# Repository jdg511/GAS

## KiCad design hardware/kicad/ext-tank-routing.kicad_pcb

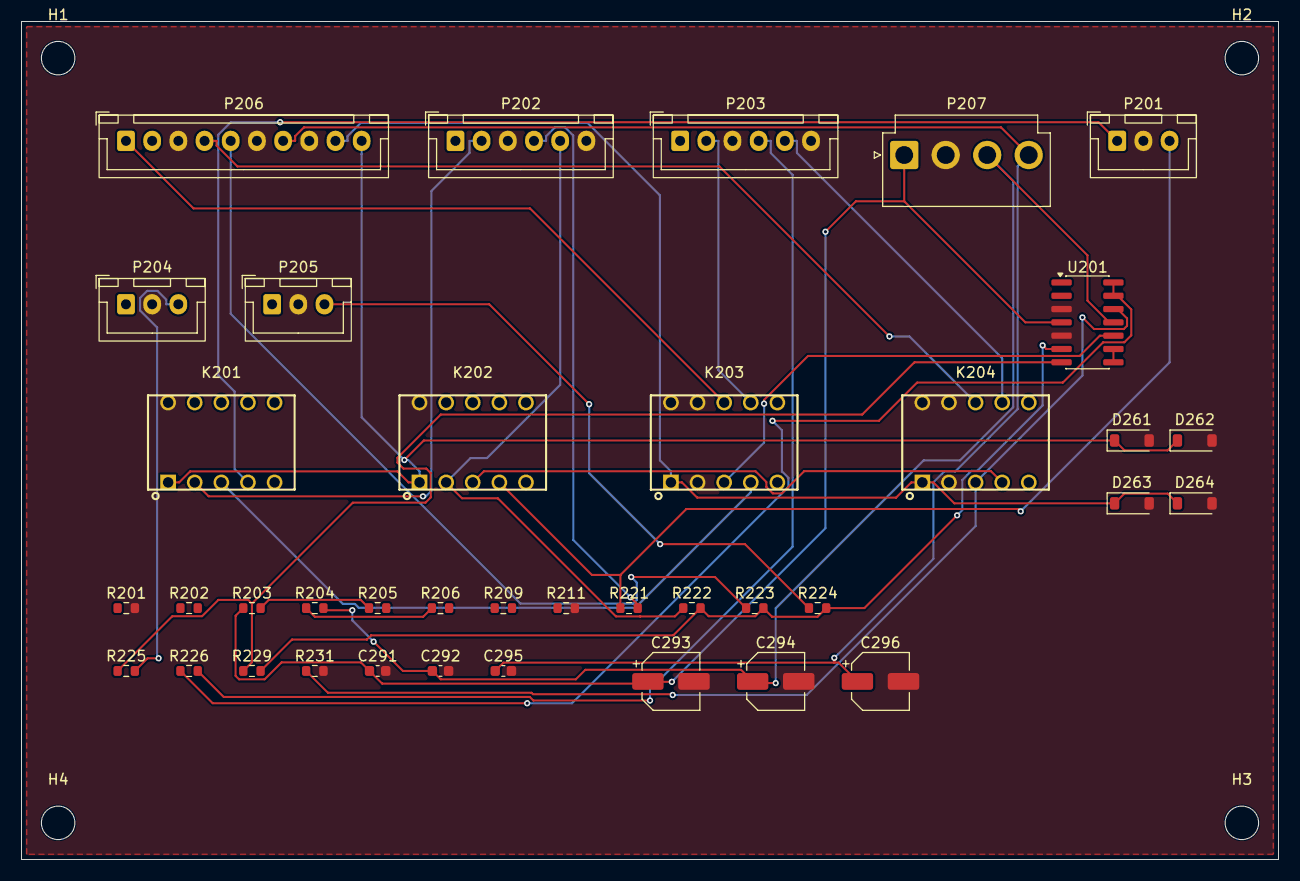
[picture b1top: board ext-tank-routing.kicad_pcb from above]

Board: 2 copper layers, 120.0 x 80.0 mm, 42 parts (0 on the bottom side), 29 nets.

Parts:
C291, C292, C295: 100nF; C_0603_1608Metric
C293, C294, C296: 10uF; CP_Elec_5x5.8
D261, D262, D263, D264: 1N4148W; D_SOD-123
H1, H2, H3, H4: M3 NPTH; MountingHole_3.2mm_M3
K201, K202, K203, K204: TQ2-5V; Relay_DPDT_Panasonic_TQ2
P201: JIO-WETSEND; JST_XH_B3B-XH-A_1x03_P2.50mm_Vertical
P202: JTR-PRI; JST_XH_B6B-XH-A_1x06_P2.50mm_Vertical
P203: JTR-SEC; JST_XH_B6B-XH-A_1x06_P2.50mm_Vertical
P204: JTR-XFADE; JST_XH_B3B-XH-A_1x03_P2.50mm_Vertical
P205: JFB-INJ; JST_XH_B3B-XH-A_1x03_P2.50mm_Vertical
P206: JER-CTRL; JST_XH_B10B-XH-A_1x10_P2.50mm_Vertical
P207: JER-PWR; JST_VH_B4P-VH_1x04_P3.96mm_Vertical
R201, R205, R206, R221, R225, R226: 100R; R_0603_1608Metric
R202, R203, R204, R209, R222, R223, R224, R229: 20k; R_0603_1608Metric
R211, R231: 100k; R_0603_1608Metric
U201: OPA1679IDR; SOIC-14_3.9x8.7mm_P1.27mm

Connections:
+5VAUX: C295.1, C296.1, P206.7, P207.4
+15VA: C291.1, C293.1, P207.1, R203.1, U201.4
-15VA: C292.1, C294.1, P207.3, R204.2, U201.11
AGND: C291.2, C292.2, C293.2, C294.2, C295.2, C296.2, D261.2, D262.2, D263.2, D264.2, K201.A2, K202.A2, K203.12, K203.22, K203.A2, K204.12, K204.22, K204.A2, P201.2, P202.3, P202.6, P203.3, P203.6, P204.2, P205.2, P206.3, P206.6, P206.8, P207.2, R201.2, R211.2, R231.2, U201.3, U201.5
CTL_EXT_MODE_A: D263.1, D264.1, K203.A1, K204.A1, P206.9
CTL_EXT_MODE_B: D261.1, D262.1, K201.A1, K202.A1, P206.10
EXTMIX_L_HI: K203.21, P206.1
EXTMIX_R_HI: K204.21, P206.4
EXTMIX_R_WIPER: P206.5, R223.1
FB_RET_R: P205.3, R224.1
PRI_RET_L: K201.12, P202.2
PRI_RET_R: K202.12, P202.5, R222.1
PRI_SEND_R: P202.4, R221.2
PR_BIAS_A: R203.2, R205.1
PR_BIAS_B: R204.1, R206.1
SEC_DRV_L: K203.11, U201.10
SEC_DRV_R: K204.11, R231.1, U201.12
SEC_RET_L: K203.24, P203.2
SEC_RET_R: K204.24, P203.5
SEC_SEL_L: K201.11, K203.14
SEC_SEL_R: K202.11, K204.14
SEC_SEND_R: P203.4, R226.2
TANK_MIX_R: P204.3, R225.2
U201B_M: R222.2, R223.2, R224.2, R229.2, U201.6
U201B_OUT: R225.1, R229.1, U201.7
U201C_OUT: U201.8, U201.9
U201D_OUT: R226.1, U201.13, U201.14
WET_SEND_L: K201.14, P201.1
WET_SEND_R: K202.14, P201.3, R221.1

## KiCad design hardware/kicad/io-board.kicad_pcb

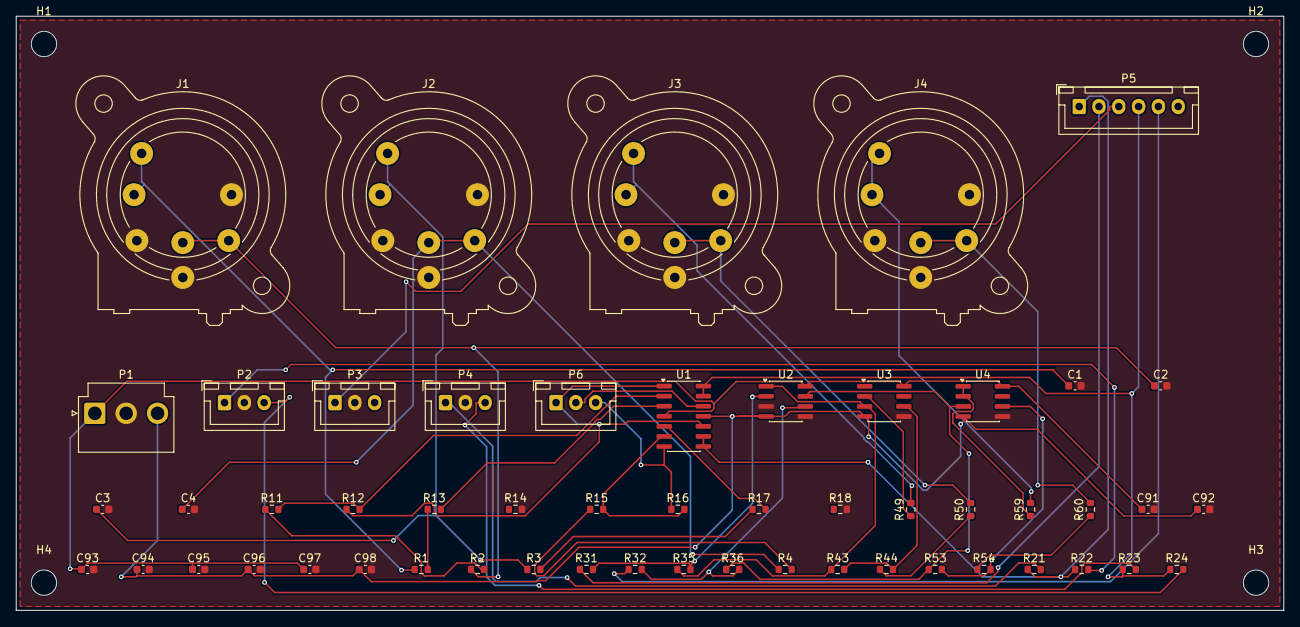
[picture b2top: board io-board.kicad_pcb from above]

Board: 2 copper layers, 160.0 x 75.0 mm, 58 parts (0 on the bottom side), 41 nets.

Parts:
C1, C2, C3, C4: 220p DNP; C_0603_1608Metric
C91, C92, C93, C94, C95, C96, C97, C98: 100n; C_0603_1608Metric
H1, H2, H3, H4: M3 NPTH; MountingHole_3.2mm_M3
J1, J2, J3, J4: NCJ6FI-S; Jack_XLR-6.35mm_Neutrik_NCJ6FI-V_Vertical
P1: JIO-PWR; JST_VH_B3P-VH_1x03_P3.96mm_Vertical
P2: JIO-WETSEND; JST_XH_B3B-XH-A_1x03_P2.50mm_Vertical
P3: JIO-WETRET; JST_XH_B3B-XH-A_1x03_P2.50mm_Vertical
P4: JIO-DRY; JST_XH_B3B-XH-A_1x03_P2.50mm_Vertical
P5: Wet/Dry control; JST_XH_B6B-XH-A_1x06_P2.50mm_Vertical
P6: Mono switch; JST_XH_B3B-XH-A_1x03_P2.50mm_Vertical
R1, R2, R3, R4, R21, R22, R23, R24: 100R; R_0603_1608Metric
R11, R12, R13, R14, R15, R16, R17, R18: 10k 0.1%; R_0603_1608Metric
R31, R32, R35, R36: 20k; R_0603_1608Metric
R43, R44, R53, R54: 10k; R_0603_1608Metric
R49, R50, R59, R60: 49.9R; R_0603_1608Metric
U1: OPA1644AIDR; SOIC-14_3.9x8.7mm_P1.27mm
U2, U3, U4: OPA1656IDR; SOIC-8_3.9x4.9mm_P1.27mm

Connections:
+15VA: C91.1, C93.1, C95.1, C97.1, P1.1, U1.4, U2.8, U3.8, U4.8
-15VA: C92.1, C94.1, C96.1, C98.1, P1.3, U1.11, U2.4, U3.4, U4.4
AGND: C1.2, C2.2, C3.2, C4.2, C91.2, C92.2, C93.2, C94.2, C95.2, C96.2, C97.2, C98.2, J1.1, J1.G, J1.S, J2.1, J2.G, J2.S, J3.1, J3.G, J3.S, J4.1, J4.G, J4.S, P1.2, P2.2, P3.2, P4.2, R14.2, R18.2, U2.3, U2.5, U3.5, U4.5
DRY_L: P4.1, R21.2
DRY_R: P4.3, R23.2
INBUF_L_N: R2.2, R11.1
INBUF_L_P: R1.2, R13.1
INBUF_R_N: R4.2, R15.1
INBUF_R_P: R3.2, R17.1
IN_BAL_L_N: C2.1, J1.3, J1.R, R2.1
IN_BAL_L_P: C1.1, J1.2, J1.T, R1.1
IN_BAL_R_N: C4.1, J2.3, J2.R, R4.1
IN_BAL_R_P: C3.1, J2.2, J2.T, R3.1
L_BLEND: R35.1, R43.1, U2.1, U3.3
L_PROG: P5.1, R21.1, R22.1, U1.8, U1.9
L_RX: P6.1, R12.1, U1.1, U1.10
L_RX_M: R11.2, R12.2, U1.2
L_RX_P: R13.2, U1.3
MONO_C: P6.2, U1.12
OUT_BAL_L_N: J3.3, J3.R, R50.2
OUT_BAL_L_P: J3.2, J3.T, R49.2
OUT_BAL_R_N: J4.3, J4.R, R60.2
OUT_BAL_R_P: J4.2, J4.T, R59.2
R_BLEND: R36.1, R53.1, U2.7, U4.3
R_PROG: P5.4, R23.1, R24.1, U1.13, U1.14
R_RX: P6.3, R16.1, U1.7
R_RX_M: R15.2, R16.2, U1.6
R_RX_P: R17.2, U1.5
U2A_M: R31.2, R35.2, U2.2
U2B_M: R32.2, R36.2, U2.6
U3A_OUT: R49.1, U3.2
U3B_M: R43.2, R44.2, U3.6
U3B_OUT: R44.1, R50.1
U4A_OUT: R59.1, U4.1, U4.2
U4B_M: R53.2, R54.2, U4.6
U4B_OUT: R54.1, R60.1
WD_L_WIPER: P5.2, R31.1
WD_R_WIPER: P5.5, R32.1
WET_SEND_L: P2.1, R22.2
WET_SEND_R: P2.3, R24.2
WET_SUM_L: P3.1, P5.3

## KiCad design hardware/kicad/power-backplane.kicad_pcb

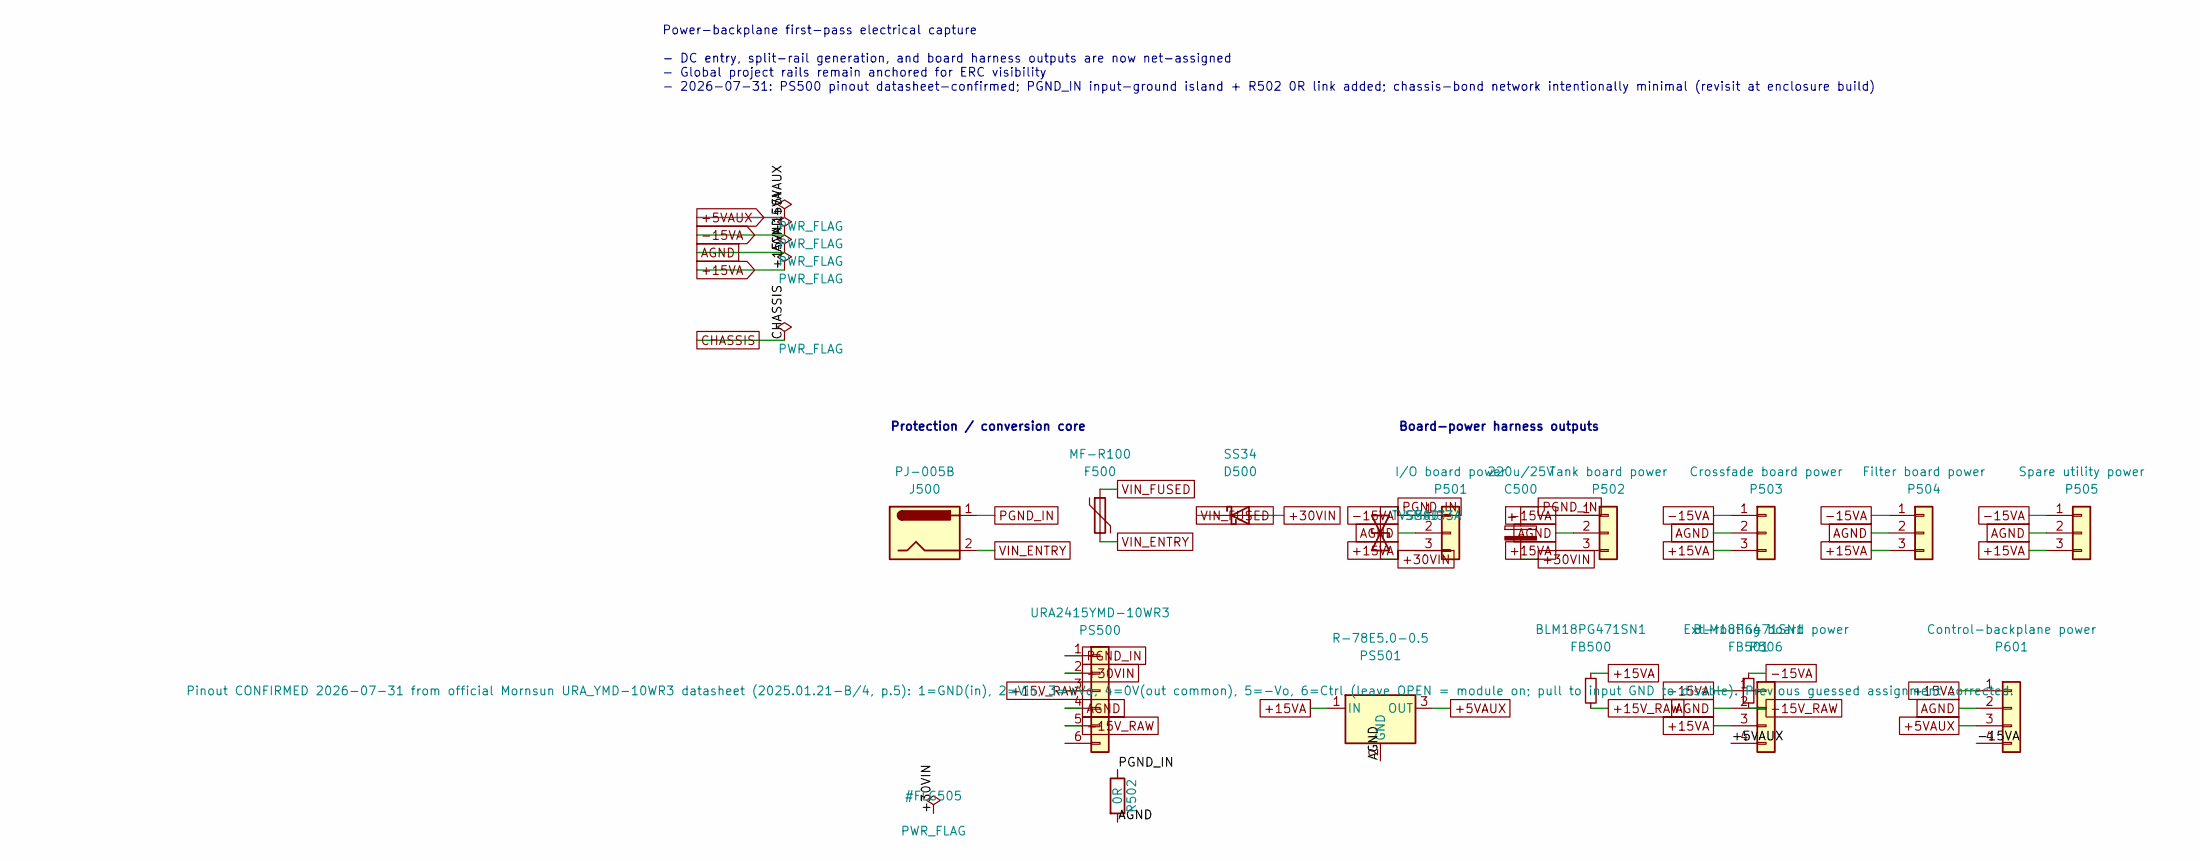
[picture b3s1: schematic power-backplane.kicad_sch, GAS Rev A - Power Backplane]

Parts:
C500: 220u/25V; CP_Elec_8x10.5
D500: SS34; D_SMA
F500: MF-R100; Fuse_1812_4532Metric
FB500, FB501: BLM18PG471SN1; L_0603_1608Metric
J500: PJ-005B; BarrelJack_Horizontal
P501: I/O board power; JST_VH_B3P-VH_1x03_P3.96mm_Vertical
P502: Tank board power; JST_VH_B3P-VH_1x03_P3.96mm_Vertical
P503: Crossfade board power; JST_VH_B3P-VH_1x03_P3.96mm_Vertical
P504: Filter board power; JST_VH_B3P-VH_1x03_P3.96mm_Vertical
P505: Spare utility power; JST_VH_B3P-VH_1x03_P3.96mm_Vertical
P506: Ext-routing board power; JST_VH_B4P-VH_1x04_P3.96mm_Vertical
P601: Control-backplane power; JST_VH_B4P-VH_1x04_P3.96mm_Vertical
PS500: URA2415YMD-10WR3; Converter_DCDC_Mornsun_URA_YMD_THT
PS501: R-78E5.0-0.5; Converter_DCDC_RECOM_R-78E-0.5_THT
R502: 0R; R_0603_1608Metric
TVS500: SMAJ33A; D_SMA

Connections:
+5VAUX: P506.4, P601.3, PS501.3 (OUT)
+15VA: FB500.1, P501.3, P502.3, P503.3, P504.3, P505.3, P506.3, P601.1, PS501.1 (IN)
+15V_RAW: FB500.2, PS500.3
+30VIN: C500.2, D500.2 (A), PS500.2, TVS500.2 (A2)
-15VA: FB501.1, P501.1, P502.1, P503.1, P504.1, P505.1, P506.1, P601.4
-15V_RAW: FB501.2, PS500.5
AGND: P501.2, P502.2, P503.2, P504.2, P505.2, P506.2, P601.2, PS500.4, PS501.2 (GND), R502.2
PGND_IN: C500.1, J500.1, PS500.1, R502.1, TVS500.1 (A1)
VIN_ENTRY: F500.2, J500.2
VIN_FUSED: D500.1 (K), F500.1

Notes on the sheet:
Power-backplane first-pass electrical capture - DC entry, split-rail generation, and board harness outputs are now net-assigned - Global project rails remain anchored for ERC visibility - 2026-07-31: PS500 pinout datasheet-confirmed; PGND_IN input-ground island + R502 0R link added; chassis-bond ne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
Protection / conversion core
Board-power harness outputs

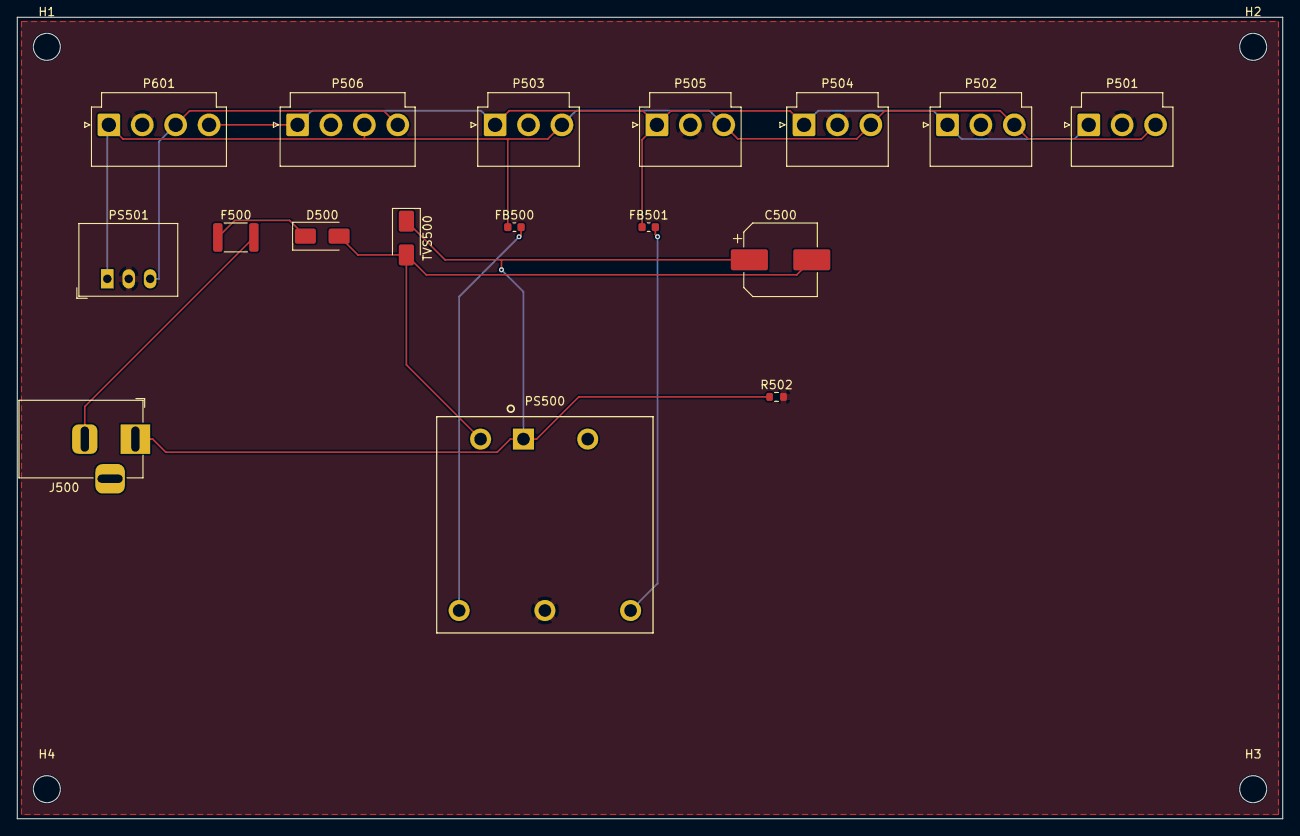
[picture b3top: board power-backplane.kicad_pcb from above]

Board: 2 copper layers, 150.0 x 95.0 mm, 21 parts (0 on the bottom side), 10 nets.

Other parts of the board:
H1, H2, H3, H4: M3 NPTH; MountingHole_3.2mm_M3

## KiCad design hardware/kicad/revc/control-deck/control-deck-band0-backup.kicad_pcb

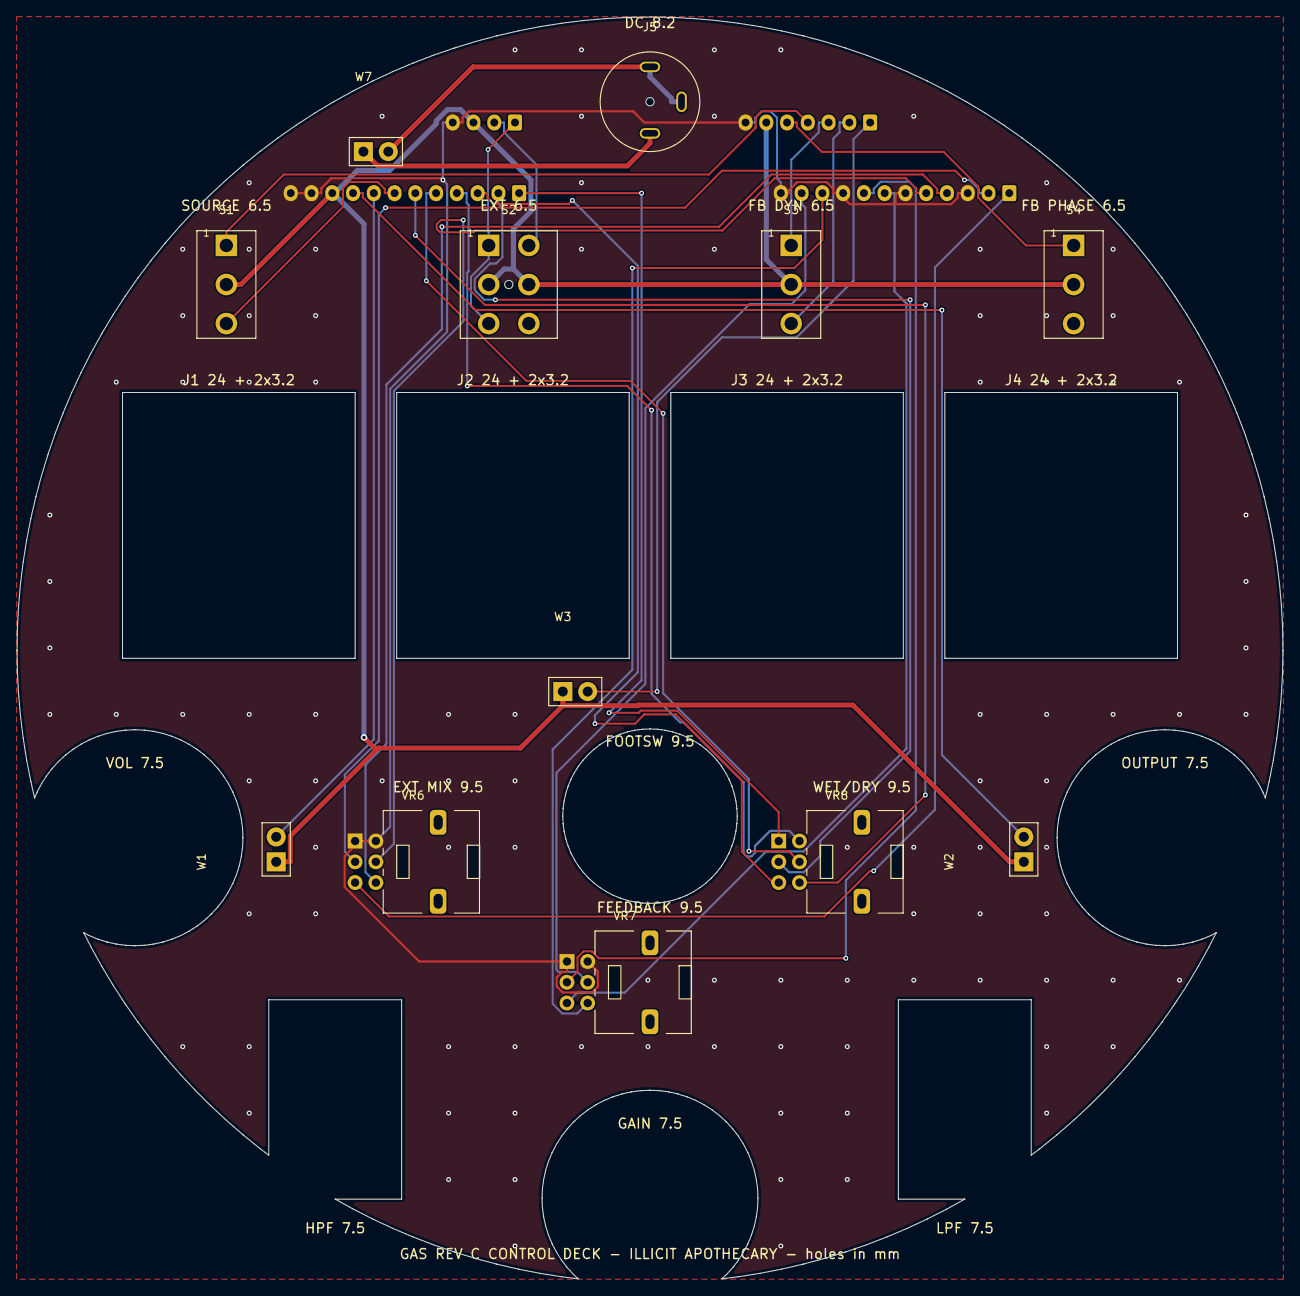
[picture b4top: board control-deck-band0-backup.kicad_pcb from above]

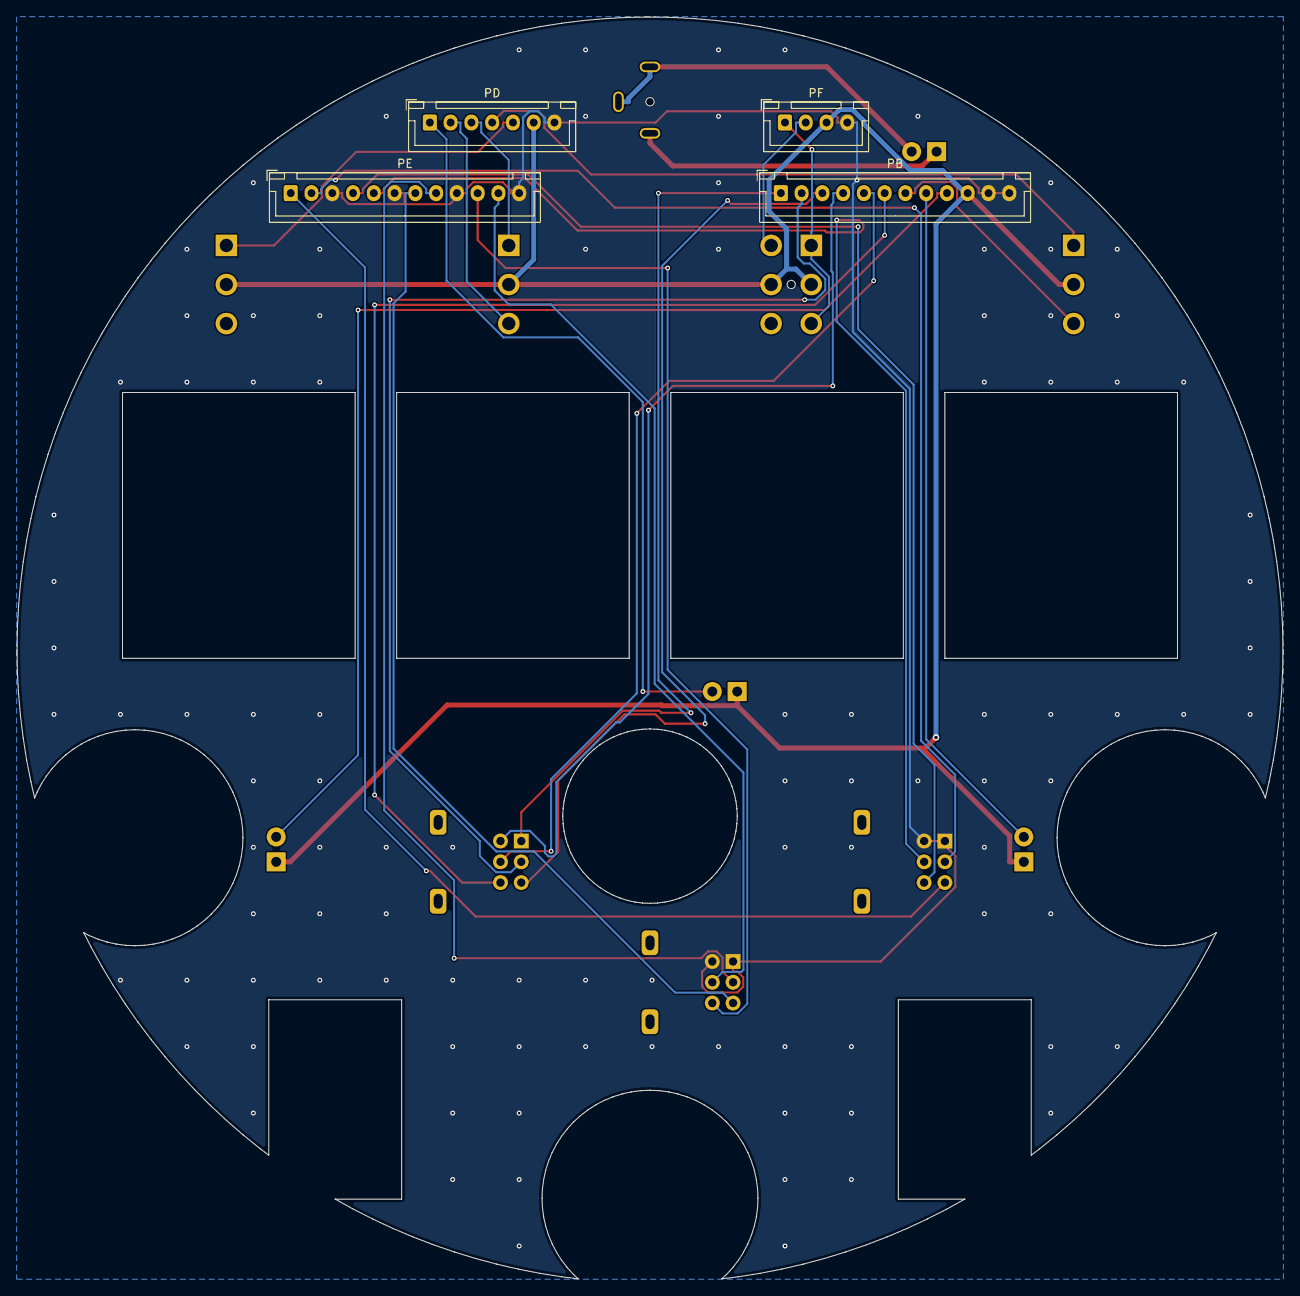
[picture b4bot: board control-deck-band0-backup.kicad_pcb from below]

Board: 2 copper layers, 152.4 x 151.9 mm, 16 parts (4 on the bottom side), 28 nets.

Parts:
J5: DC IN 24-30 V centre +; BarrelJack_SameSky_PJ-064B_Vertical
PB: to io-board P5 (Wet/Dry, switch lines); JST_XH_B12B-XH-A_1x12_P2.50mm_Vertical
PD: to circuit-board P8 (switch lines); JST_XH_B7B-XH-A_1x07_P2.50mm_Vertical
PE: to circuit-board P7 (Ext Mix, Feedback); JST_XH_B12B-XH-A_1x12_P2.50mm_Vertical
PF: to tank-board P5 (Ext tanks toggle); JST_XH_B4B-XH-A_1x04_P2.50mm_Vertical
S1: Source: up Mono>Stereo / centre Stereo / down MEG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; SW_Toggle_CK7000_SPDT_PC_Vertical
S2: Ext tanks: up Series / centre Off / down Parallel; SW_Toggle_CK7000_DPDT_PC_Vertical
S3: FB Dyn: up Comp / centre Off / down Limit; SW_Toggle_CK7000_SPDT_PC_Vertical
S4: FB Phase: up normal / down inverted; SW_Toggle_CK7000_SPDT_PC_Vertical
VR6: Ext Mix; Potentiometer_Alps_RK09L_Double_Vertical
VR7: Feedback; Potentiometer_Alps_RK09L_Double_Vertical
VR8: Wet/Dry (CW = wet); Potentiometer_Alps_RK09L_Double_Vertical
W1: VR1 Vol push-pull switch: common, NO; WirePads_1x02_P3.0mm_D1.2mm
W2: VR5 Output push-pull switch: common, NO; WirePads_1x02_P3.0mm_D1.2mm
W3: VR3 Gain push-pull switch: common, NO; WirePads_1x02_P3.0mm_D1.2mm
W7: DC cable to power-board P1 (VH-2): centre +, slee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; WirePads_1x02_P3.0mm_D1.2mm

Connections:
+5VAUX: PB.10, PD.6, PF.3, S1.2, S2.2, S2.5, S3.2, S4.2, W1.1, W2.1, W3.1
AGND: PB.11, PB.12, PD.7, PE.3, PE.6, PE.9, PE.12, PF.4, VR6.1, VR6.4, VR7.1, VR7.4
CTL_COMP: PD.2, S3.3
CTL_DIRT: PD.1, W3.2
CTL_EXT_A: PF.1, S2.1, S2.3
CTL_EXT_B: PF.2, S2.4
CTL_FB_INV: PD.5, S4.1
CTL_LIMIT: PD.3, S3.1
CTL_MEGA: PD.4, S1.1
CTL_MONO: PB.7, S1.3
CTL_TAPE: PB.9, W2.2
CTL_TUBE: PB.8, W1.2
EXM_L_W: PE.2, VR6.2
EXM_R_W: PE.5, VR6.5
FBP_L_W: PE.8, VR7.2
FBP_R_W: PE.11, VR7.5
L_PROG: PB.1, VR8.1
PGND: J5.2, J5.3, W7.2
R_PROG: PB.4, VR8.4
SEC_BUF_L: PE.1, VR6.3
SEC_BUF_R: PE.4, VR6.6
VIN_RAW: J5.1, W7.1
WD_L_W: PB.2, VR8.2
WD_R_W: PB.5, VR8.5
WET_L: PB.3, VR8.3
WET_R: PB.6, VR8.6
WET_RAW_L: PE.7, VR7.3
WET_RAW_R: PE.10, VR7.6
